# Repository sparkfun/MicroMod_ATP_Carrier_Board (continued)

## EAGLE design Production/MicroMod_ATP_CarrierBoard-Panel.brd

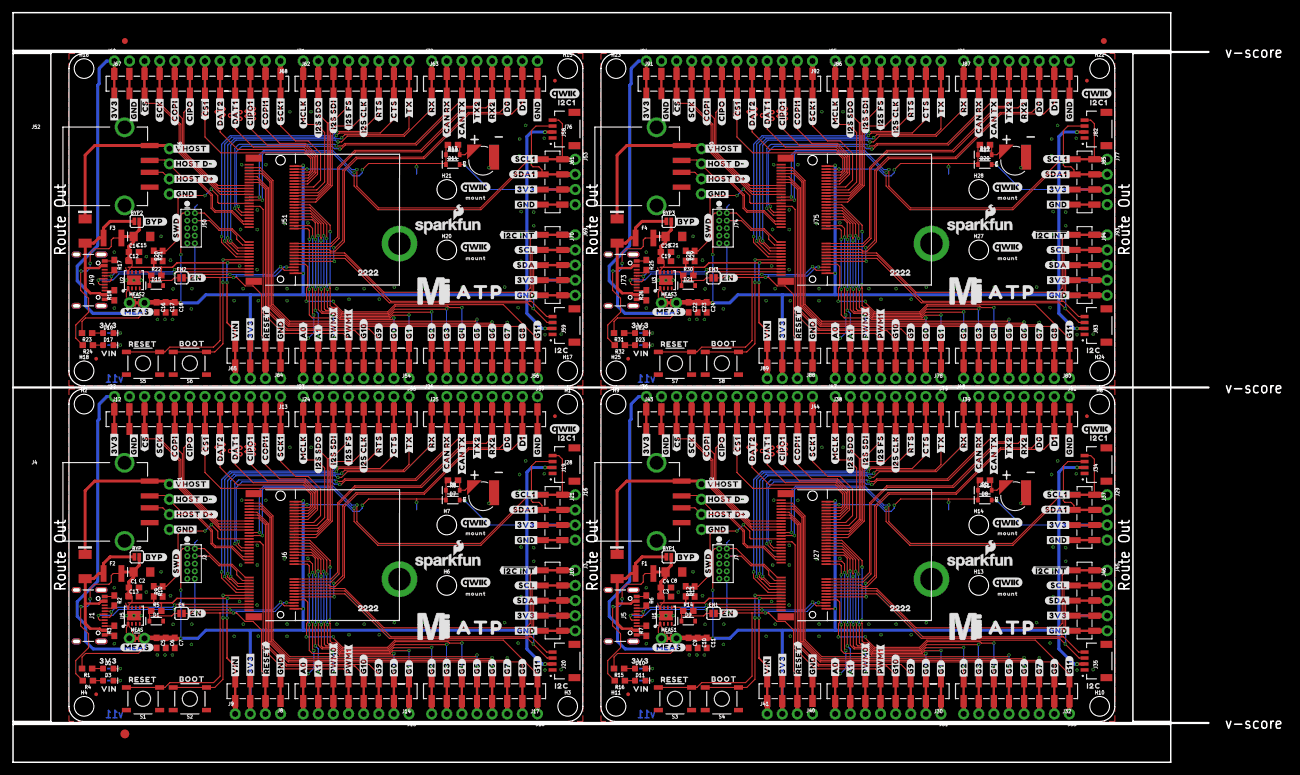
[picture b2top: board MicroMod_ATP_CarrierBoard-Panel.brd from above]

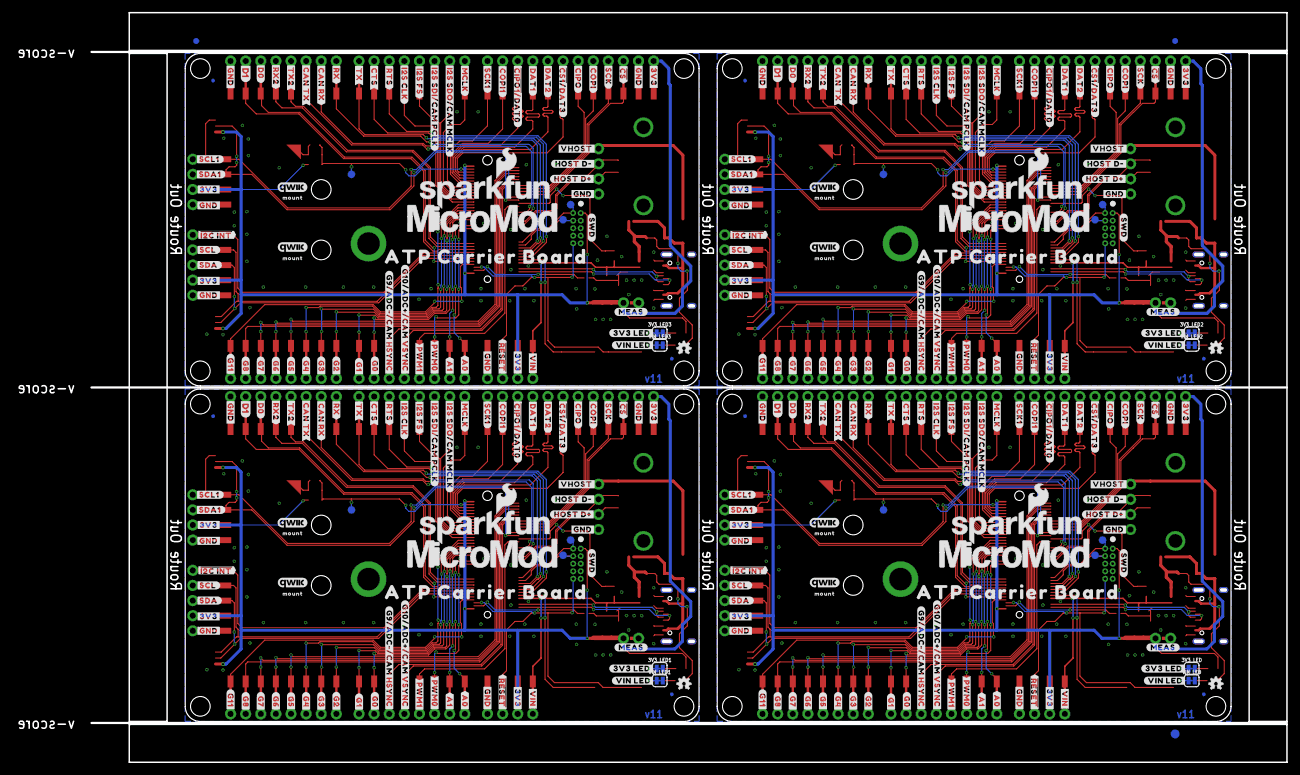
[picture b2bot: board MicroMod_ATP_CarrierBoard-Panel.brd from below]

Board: 2 copper layers, 200.9 x 126.0 mm, 890 parts (323 on the bottom side), 284 nets.

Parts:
3V3_LED, 3V3_LED1, 3V3_LED2, 3V3_LED3: JUMPER-SMT_2_NC_TRACE_SILK; SMT-JUMPER_2_NC_TRACE_SILK
BT1, BT2, BT3, BT4: ML414H; ML414H_IV01E
BYP, BYP1, BYP2, BYP3: JUMPER-SMT_2_NO_SILK; SMT-JUMPER_2_NO_SILK
C1, C4, C6, C10, C14, C17, C20, C23: 0.1uF; 0603
C2, C8, C15, C21: 10uF; EIA3216
C3, C7, C11, C12, C13, C18, C19, C24: 0.22uF; 0603
C5, C9, C16, C22: 1.0uF; 0603
D1, D9, D15, D21: 3.3V; SOD-323
D2, D3, D10, D11, D16, D17, D22, D23: RED; LED-0603
D4, D12, D18, D24: 1A/15V/220mV; DO-214BA
D5, D6, D13, D19: 3A/10V/280mV; SOD-323
D7, D8, D14, D20: 1A/23V/620mV; SOD-323
E$1, E$2, E$3, E$4: FIDUCIAL-1X2
E$5, E$6: FIDUCIAL-1.5X3
EN, EN1, EN2, EN3: JUMPER-SMT_2_NO_SILK; SMT-JUMPER_2_NO_SILK
F1, F2, F3, F4: 6V/2A; 1210
FD1, FD2, FD3, FD4, FD5, FD6, FD7, FD8, FD9, FD10, FD11, FD12, FD13, FD14, FD15, FD16: FIDUCIALUFIDUCIAL; FIDUCIAL-MICRO
H1, H2, H3, H4, H6, H7, H8, H9, H10, H11, H13, H14, H15, H16, H17, H18, H20, H21, H22, H23, H24, H25, H27, H28: STAND-OFF
H5, H12, H19, H26: STAND-OFF-REFLOW2.5MM_TALL; STAND-OFF-REFLOW-M2.5
J1, J5, J49, J73: USB-C-16P-2LAYER-PADS
J2, J7, J50, J74: JTAG; 2X5-PTH-1.27MM
J3, J45, J69, J93: 1X05_NO_SILK
J4, J28, J52, J76: USB_A_SMT_FEMALE; USB-A-S-SILK-FEMALE
J6, J27, J51, J75: MICROMOD-2222-C; M.2-CONNECTOR-E
J8, J21, J37, J40, J61, J64, J85, J88: 1X04_SMD_STRAIGHT_COMBO; 1X04_SMD_VERTICAL_COMBO
J9, J11, J16, J22, J29, J36, J41, J42, J53, J60, J65, J66, J77, J84, J89, J90: 1X04_NO_SILK
J10, J46, J70, J94: 1X05_SMD_VERTICAL_COMBO
J12, J43, J67, J91: 1X12_SMD_COMBINED
J13, J15, J18, J23, J26, J31, J33, J44, J47, J48, J55, J57, J68, J71, J72, J79, J81, J92, J95, J96: 1X08_NO_SILK
J14, J17, J24, J25, J30, J32, J38, J39, J54, J56, J62, J63, J78, J80, J86, J87: 1X08_SMD_COMBINED
J19, J20, J34, J35, J58, J59, J82, J83: QWIIC_RIGHT_ANGLE; JST04_1MM_RA
LOGO1, LOGO11, LOGO19, LOGO27: SFE_LOGO_NAME_FLAME.1_INCH; SFE_LOGO_NAME_FLAME_.1
LOGO2, LOGO15, LOGO23, LOGO31: QWIIC_LOGO_5MM; QWIIC_5MM
LOGO3, LOGO9, LOGO17, LOGO25: OSHW-LOGOMINI; OSHW-LOGO-MINI
LOGO4, LOGO10, LOGO18, LOGO26: SFE_LOGO_NAME_FLAME.2_INCH; SFE_LOGO_NAME_FLAME_.2
LOGO5, LOGO6, LOGO7, LOGO8, LOGO12, LOGO13, LOGO14, LOGO16, LOGO20, LOGO21, LOGO22, LOGO24, LOGO28, LOGO29, LOGO30, LOGO32: QWIIC_LOGO_3MM; QWIIC_5MM
MEAS, MEAS1, MEAS2, MEAS3: COMBO-JUMPER_2_NC_TRACE
R1, R4, R8, R11, R15, R16, R19, R23, R24, R27, R31, R32: 1k; 0603
R2, R3, R6, R7, R17, R18, R25, R26: 5.1k; 0603
R5, R14, R22, R30: 100k; 0603
R9, R12, R20, R28: 10k; 0603
R10, R13, R21, R29: 20k; 0603
S1, S3, S5, S7: Reset; TACTILE_SWITCH_SMD_5.2MM
S2, S4, S6, S8: BOOT; TACTILE_SWITCH_SMD_5.2MM
TP1, TP2, TP3, TP4, TP5, TP6, TP7, TP8, TP9, TP10, TP11, TP12: TEST-POINT3X5; PAD.03X.05
U1, U2, U3, U5: AP7361C-33; UDFN-8
U$1, U$123, U$169, U$251, U$314, U$396, U$459, U$541: #A0#10
U$2, U$124, U$170, U$252, U$315, U$397, U$460, U$542: #A1#10
U$3, U$27, U$46, U$47, U$58, U$89, U$100, U$101, U$102, U$103, U$104, U$105, U$160, U$166, U$167, U$228, U$229, U$230, U$231, U$232, U$233, U$268, U$269, U$270, U$305, U$311, U$312, U$373, U$374, U$375, U$376, U$377, U$378, U$413, U$414, U$415, U$450, U$456, U$457, U$518, U$519, U$520, U$521, U$522, U$523, U$558, U$559, U$560: #GND#0
U$4, U$120, U$172, U$248, U$317, U$393, U$462, U$538: #G0#2
U$5, U$163, U$308, U$453: #RESET10
U$6, U$98, U$171, U$227, U$316, U$372, U$461, U$517: #D0#0
U$7, U$119, U$173, U$247, U$318, U$392, U$463, U$537: #G1#2
U$8, U$118, U$174, U$246, U$319, U$391, U$464, U$536: #G2#2
U$9, U$117, U$175, U$245, U$320, U$390, U$465, U$535: #G3#3
U$10, U$116, U$176, U$244, U$321, U$389, U$466, U$534: #G4#4
U$11, U$115, U$177, U$243, U$322, U$388, U$467, U$533: #G5#5
U$12, U$114, U$178, U$242, U$323, U$387, U$468, U$532: #G6#6
U$13, U$113, U$179, U$241, U$324, U$386, U$469, U$531: #G7#7
U$14, U$112, U$180, U$240, U$325, U$385, U$470, U$530: #G8#8
U$15, U$181, U$326, U$471: #G9#9
U$16, U$182, U$327, U$472: #G10#10
U$17, U$111, U$183, U$239, U$328, U$384, U$473, U$529: #G11#10
U$18, U$121, U$184, U$249, U$329, U$394, U$474, U$539: #PWM0#10
U$19, U$122, U$185, U$250, U$330, U$395, U$475, U$540: #PWM1#10
U$20, U$286, U$431, U$576: ##CS1##5178039
U$21, U$110, U$238, U$271, U$383, U$416, U$528, U$561: ##I2C_INT##10
U$22, U$130, U$292, U$437: #CAN_RX#9
U$23, U$97, U$148, U$226, U$293, U$371, U$438, U$516: #CAN_TX#10
U$24, U$149, U$294, U$439: #CIPO#3
U$25, U$150, U$295, U$440: #COPI#2
U$26, U$151, U$296, U$441: #CTS#6
U$28, U$267, U$412, U$557: #SCK#2
U$29, U$152, U$297, U$442: #I2S_FS#5
U$30, U$153, U$298, U$443: #I2S_SDI#5
U$31, U$154, U$299, U$444: #I2S_SDO#5
U$32, U$155, U$300, U$445: #MCLK#4
U$33, U$156, U$301, U$446: #RTS#5
U$34, U$157, U$302, U$447: #RX#8
U$35, U$158, U$303, U$448: #TX#7
U$36, U$287, U$432, U$577: #DAT1#5178039
U$37, U$125, U$206, U$253, U$351, U$398, U$496, U$543: ##RESET##7
U$38, U$60, U$61, U$70, U$88, U$106, U$107, U$126, U$197, U$198, U$199, U$200, U$234, U$235, U$254, U$266, U$342, U$343, U$344, U$345, U$379, U$380, U$399, U$411, U$487, U$488, U$489, U$490, U$524, U$525, U$544, U$556: #3V3#1
U$39, U$159, U$304, U$449: #BYP#8
U$40, U$128, U$161, U$256, U$306, U$401, U$451, U$546: #HOST_D##9
U$41, U$129, U$162, U$257, U$307, U$402, U$452, U$547: #HOST_D##10
U$42, U$132, U$186, U$259, U$331, U$404, U$476, U$549: #MEAS#10
U$43, U$164, U$309, U$454: BOOT10
U$44, U$108, U$187, U$236, U$332, U$381, U$477, U$526: #SDA#4
U$45, U$127, U$165, U$255, U$310, U$400, U$455, U$545: #VIN#6
U$48, U$280, U$425, U$570: #EN#0
U$49, U$109, U$168, U$237, U$313, U$382, U$458, U$527: #SCL#5
U$50, U$146, U$281, U$282, U$426, U$427, U$571, U$572: #VHOST#0
U$51, U$131, U$188, U$258, U$333, U$403, U$478, U$548: #SWD#10
U$52, U$189, U$334, U$479: #I2S_CLK#5
U$53, U$288, U$433, U$578: #DAT2#5178039
U$54, U$289, U$434, U$579: #CIPO1#5178039
U$55, U$74, U$291, U$436: 22229
U$56, U$290, U$435, U$580: ##CIPO1##DAT0#5178038
U$57, U$75, U$205, U$208, U$350, U$353, U$495, U$498: #COPI1#2
U$59, U$207, U$352, U$497: ##CS##0
U$62, U$201, U$346, U$491: ATP0
U$63, U$76, U$190, U$209, U$335, U$354, U$480, U$499: #RX2#3
U$64, U$80, U$191, U$213, U$336, U$358, U$481, U$503: #TX2#2
U$65, U$78, U$192, U$211, U$337, U$356, U$482, U$501: #SCL1#3
U$66, U$79, U$193, U$212, U$338, U$357, U$483, U$502: #SDA1#3
U$67, U$77, U$194, U$210, U$339, U$355, U$484, U$500: #SCK1#2
U$68, U$195, U$340, U$485: VIN3
U$69, U$196, U$341, U$486: 3V34
U$71, U$202, U$347, U$492: I2C4
U$72, U$203, U$348, U$493: I2C14
U$73, U$204, U$349, U$494: ATP_CARRIER_BOARD1
U$81, U$283, U$428, U$573: ##CS##5178037
U$82, U$214, U$359, U$504: #DAT2#5
U$83, U$215, U$360, U$505: #DAT1#5
U$84, U$284, U$429, U$574: ##CS1##DAT3#5178037
U$85, U$216, U$361, U$506: #COPI#4
U$86, U$217, U$362, U$507: #SCK#4
U$87, U$218, U$363, U$508: #MCLK#6
U$90, U$219, U$364, U$509: #I2S_FS#7
U$91, U$220, U$365, U$510: #I2S_CLK#7
U$92, U$221, U$366, U$511: #RTS#7
U$93, U$222, U$367, U$512: #CTS#8
U$94, U$223, U$368, U$513: #TX#9
U$95, U$224, U$369, U$514: #RX#10
U$96, U$225, U$370, U$515: #CAN_RX#10
U$99, U$145, U$272, U$279, U$417, U$424, U$562, U$569: D10
U$133, U$260, U$405, U$550: #VIN_LED#10
U$134, U$261, U$406, U$551: #3V3_LED#10
U$135, U$262, U$407, U$552: #G9#ADC##CAM_HSYNC#9
U$136, U$263, U$408, U$553: #G10#ADC##CAM_VSYNC#10
U$137, U$264, U$409, U$554: #I2S_SDI#CAM_PCLK#7
U$138, U$265, U$410, U$555: #I2S_SDO#CAM_MCLK#7
U$139, U$141, U$142, U$143, U$274, U$275, U$276, U$277, U$419, U$420, U$421, U$422, U$564, U$565, U$566, U$567: MOUNT10
U$140, U$273, U$418, U$563: MICROMOD_MI_LOGO_1
U$144, U$278, U$423, U$568: MICROMOD_LOGO_1
U$147, U$285, U$430, U$575: #CIPO#5178038
VIN_LED, VIN_LED1, VIN_LED2, VIN_LED3: JUMPER-SMT_2_NC_TRACE_SILK; SMT-JUMPER_2_NC_TRACE_SILK

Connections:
3.3V: C5.1, C6.1, C7.1, D7.A, J2.1, J3.4, J6.2, J6.74, J8.3, J9.2, J10.4, J12.1, J16.3, J19.2, J20.2, J21.3, J22.1, MEAS.2, MEAS.4, R1.2
3.3V1: C9.1, C10.1, C11.1, D8.A, J7.1, J27.2, J27.74, J29.3, J34.2, J35.2, J36.1, J37.3, J40.3, J41.2, J43.1, J45.4, J46.4, MEAS1.2, MEAS1.4, R15.2
3.3V2: C16.1, C17.1, C18.1, D14.A, J50.1, J51.2, J51.74, J53.3, J58.2, J59.2, J60.1, J61.3, J64.3, J65.2, J67.1, J69.4, J70.4, MEAS2.2, MEAS2.4, R23.2
3.3V3: C22.1, C23.1, C24.1, D20.A, J74.1, J75.2, J75.74, J77.3, J82.2, J83.2, J84.1, J85.3, J88.3, J89.2, J91.1, J93.4, J94.4, MEAS3.2, MEAS3.4, R31.2
3.3V_EN: D1.C, EN.1, R5.1, U5.5
3.3V_EN1: D9.C, EN1.1, R14.1, U1.5
3.3V_EN2: D15.C, EN2.1, R22.1, U2.5
3.3V_EN3: D21.C, EN3.1, R30.1, U3.5
!BOOT!: J6.11, S2.3, S2.4
!BOOT!1: J27.11, S4.3, S4.4
!BOOT!2: J51.11, S6.3, S6.4
!BOOT!3: J75.11, S8.3, S8.4
!CS1!/DAT1: J27.70, J43.7, J44.6
!CS1!/DAT2: J51.70, J67.7, J68.6
!CS1!/DAT3: J6.70, J12.7, J13.6
!CS1!/DAT4: J75.70, J91.7, J92.6
!CS!: J6.55, J12.3, J22.3
!CS!1: J27.55, J36.3, J43.3
!CS!2: J51.55, J60.3, J67.3
!CS!3: J75.55, J84.3, J91.3
!RESET: J2.10, J6.6, J8.2, J9.3, S1.3, S1.4
!RESET1: J7.10, J27.6, J40.2, J41.3, S3.3, S3.4
!RESET2: J50.10, J51.6, J64.2, J65.3, S5.3, S5.4
!RESET3: J74.10, J75.6, J88.2, J89.3, S7.3, S7.4
A0: J6.34, J14.8, J15.8
A1: J6.38, J14.7, J15.7
A2: J27.34, J30.8, J31.8
A3: J27.38, J30.7, J31.7
A4: J51.34, J54.8, J55.8
A5: J51.38, J54.7, J55.7
A6: J75.34, J78.8, J79.8
A7: J75.38, J78.7, J79.7
CAN_RXI: J6.41, J25.2, J26.2
CAN_RXI1: J27.41, J39.2, J48.2
CAN_RXI2: J51.41, J63.2, J72.2
CAN_RXI3: J75.41, J87.2, J96.2
CAN_TXO: J6.43, J25.3, J26.3
CAN_TXO1: J27.43, J39.3, J48.3
CAN_TXO2: J51.43, J63.3, J72.3
CAN_TXO3: J75.43, J87.3, J96.3
CIPO: J6.61, J12.6, J13.7
CIPO1: J27.61, J43.6, J44.7
CIPO1/DAT0: J6.64, J12.10, J13.3
CIPO1/DAT1: J27.64, J43.10, J44.3
CIPO1/DAT2: J51.64, J67.10, J68.3
CIPO1/DAT3: J75.64, J91.10, J92.3
CIPO2: J51.61, J67.6, J68.7
CIPO3: J75.61, J91.6, J92.7
COPI: J6.59, J12.5, J13.8
COPI1: J6.62, J12.11, J13.2
COPI2: J27.59, J43.5, J44.8
COPI3: J27.62, J43.11, J44.2
COPI4: J51.59, J67.5, J68.8
COPI5: J51.62, J67.11, J68.2
COPI6: J75.59, J91.5, J92.8
COPI7: J75.62, J91.11, J92.2
CTS1: J6.15, J23.7, J24.7
CTS2: J27.15, J38.7, J47.7
CTS3: J51.15, J62.7, J71.7
CTS4: J75.15, J86.7, J95.7
D0: J6.10, J25.6, J26.6
D1: J6.18, J25.7, J26.7
D2: J27.10, J39.6, J48.6
D3: J27.18, J39.7, J48.7
D4: J51.10, J63.6, J72.6
D5: J51.18, J63.7, J72.7
D6: J75.10, J87.6, J96.6
D7: J75.18, J87.7, J96.7
DAT1: J6.66, J12.9, J13.4
DAT2: J6.68, J12.8, J13.5
DAT3: J27.66, J43.9, J44.4
DAT4: J27.68, J43.8, J44.5
DAT5: J51.66, J67.9, J68.4
DAT6: J51.68, J67.8, J68.5
DAT7: J75.66, J91.9, J92.4
DAT8: J75.68, J91.8, J92.5
G0: J6.40, J14.2, J15.2
G1: J6.42, J14.1, J15.1
G2: J6.44, J17.8, J18.8
G3: J6.46, J17.7, J18.7
G4: J6.48, J17.6, J18.6
G5: J6.73, J17.5, J18.5
G6: J6.71, J17.4, J18.4
G7: J6.69, J17.3, J18.3
G8: J6.67, J17.2, J18.2
G9: J27.40, J30.2, J31.2
G9/ADC_N: J6.65, J14.3, J15.3
G9/ADC_N1: J27.65, J30.3, J31.3
G9/ADC_N2: J51.65, J54.3, J55.3
G9/ADC_N3: J75.65, J78.3, J79.3
G10: J27.42, J30.1, J31.1
G10/ADC_P: J6.63, J14.4, J15.4
G10/ADC_P1: J27.63, J30.4, J31.4
G10/ADC_P2: J51.63, J54.4, J55.4
G10/ADC_P3: J75.63, J78.4, J79.4
G11: J6.8, J17.1, J18.1
G12: J27.73, J32.5, J33.5
G13: J27.48, J32.6, J33.6
G14: J27.44, J32.8, J33.8
G15: J27.69, J32.3, J33.3
G16: J27.46, J32.7, J33.7
G17: J27.71, J32.4, J33.4
G18: J27.67, J32.2, J33.2
G19: J27.8, J32.1, J33.1
G20: J51.40, J54.2, J55.2
G21: J51.42, J54.1, J55.1
G22: J51.73, J56.5, J57.5
G23: J51.48, J56.6, J57.6
G24: J51.44, J56.8, J57.8
G25: J51.69, J56.3, J57.3
G26: J51.46, J56.7, J57.7
G27: J51.71, J56.4, J57.4
G28: J51.67, J56.2, J57.2
G29: J51.8, J56.1, J57.1
G30: J75.40, J78.2, J79.2
G31: J75.42, J78.1, J79.1
G32: J75.73, J80.5, J81.5
G33: J75.48, J80.6, J81.6
G34: J75.44, J80.8, J81.8
G35: J75.69, J80.3, J81.3
G36: J75.46, J80.7, J81.7
G37: J75.71, J80.4, J81.4
G38: J75.67, J80.2, J81.2
G39: J75.8, J80.1, J81.1
GND: 3V3_LED.2, BT1.-, C1.2, C2.-, C5.2, C6.2, C7.2, C13.2, D1.A, H5.1, J1.GND, J1.GND2, J2.3, J2.5, J2.9, J3.5, J4.GND, J4.SHLD1, J4.SHLD2, J6.1, J6.7, J6.33, J6.36, J6.39, J6.45, J6.75, J8.1, J9.4, J10.5, J11.4, J12.2, J16.4, J19.1, J20.1, J21.4, J22.2, J25.8, J26.8, R2.1, R3.1, R9.1, S1.1, S1.2, S2.1, S2.2, U5.4, U5.EP, VIN_LED.2
GND1: 3V3_LED1.2, BT2.-, C3.2, C4.2, C8.-, C9.2, C10.2, C11.2, D9.A, H12.1, J5.GND, J5.GND2, J7.3, J7.5, J7.9, J27.1, J27.7, J27.33, J27.36, J27.39, J27.45, J27.75, J28.GND, J28.SHLD1, J28.SHLD2, J29.4, J34.1, J35.1, J36.2, J37.4, J39.8, J40.1, J41.4, J42.4, J43.2, J45.5, J46.5, J48.8, R6.1, R7.1, R12.1, S3.1, S3.2, S4.1, S4.2, U1.4, U1.EP, VIN_LED1.2
GND2: 3V3_LED2.2, BT3.-, C12.2, C14.2, C15.-, C16.2, C17.2, C18.2, D15.A, H19.1, J49.GND, J49.GND2, J50.3, J50.5, J50.9, J51.1, J51.7, J51.33, J51.36, J51.39, J51.45, J51.75, J52.GND, J52.SHLD1, J52.SHLD2, J53.4, J58.1, J59.1, J60.2, J61.4, J63.8, J64.1, J65.4, J66.4, J67.2, J69.5, J70.5, J72.8, R17.1, R18.1, R20.1, S5.1, S5.2, S6.1, S6.2, U2.4, U2.EP, VIN_LED2.2
GND3: 3V3_LED3.2, BT4.-, C19.2, C20.2, C21.-, C22.2, C23.2, C24.2, D21.A, H26.1, J73.GND, J73.GND2, J74.3, J74.5, J74.9, J75.1, J75.7, J75.33, J75.36, J75.39, J75.45, J75.75, J76.GND, J76.SHLD1, J76.SHLD2, J77.4, J82.1, J83.1, J84.2, J85.4, J87.8, J88.1, J89.4, J90.4, J91.2, J93.5, J94.5, J96.8, R25.1, R26.1, R28.1, S7.1, S7.2, S8.1, S8.2, U3.4, U3.EP, VIN_LED3.2
I2C_!INT: J3.1, J6.16, J10.1
I2C_!INT1: J27.16, J45.1, J46.1
I2C_!INT2: J51.16, J69.1, J70.1
I2C_!INT3: J75.16, J93.1, J94.1
I2S_CLK: J6.50, J23.5, J24.5
I2S_CLK1: J27.50, J38.5, J47.5
I2S_CLK2: J51.50, J62.5, J71.5
I2S_CLK3: J75.50, J86.5, J95.5
I2S_SDI: J6.54, J23.3, J24.3
I2S_SDI1: J27.54, J38.3, J47.3
I2S_SDI2: J51.54, J62.3, J71.3
I2S_SDI3: J75.54, J86.3, J95.3
I2S_SDO: J6.56, J23.2, J24.2
I2S_SDO1: J27.56, J38.2, J47.2
I2S_SDO2: J51.56, J62.2, J71.2
I2S_SDO3: J75.56, J86.2, J95.2
I2S_WS: J6.52, J23.4, J24.4
I2S_WS1: J27.52, J38.4, J47.4
I2S_WS2: J51.52, J62.4, J71.4
I2S_WS3: J75.52, J86.4, J95.4
MCLK: J6.58, J23.1, J24.1
MCLK1: J27.58, J38.1, J47.1
MCLK2: J51.58, J62.1, J71.1
MCLK3: J75.58, J86.1, J95.1
unnamed: D2.A, R1.1
unnamed: D3.A, R4.1
unnamed: 3V3_LED.1, D2.C
unnamed: D3.C, VIN_LED.1
unnamed: EN.2, J6.4
unnamed: J5.A5, R6.2
unnamed: D4.C, J4.VBUS, J11.1
unnamed: J5.B5, R7.2
unnamed: BT2.+, D5.A, R11.1
unnamed: J1.A5, R2.2
unnamed: J1.B5, R3.2
unnamed: D10.A, R15.1
unnamed: D11.A, R16.1
unnamed: BT1.+, D6.A, R8.1
unnamed: 3V3_LED1.1, D10.C
unnamed: D11.C, VIN_LED1.1
unnamed: EN1.2, J27.4
unnamed: D12.C, J28.VBUS, J42.1
unnamed: J49.A5, R17.2
unnamed: J49.B5, R18.2
unnamed: BT3.+, D13.A, R19.1
unnamed: D16.A, R23.1
unnamed: D17.A, R24.1
unnamed: 3V3_LED2.1, D16.C
unnamed: D17.C, VIN_LED2.1
unnamed: EN2.2, J51.4
unnamed: D18.C, J52.VBUS, J66.1
unnamed: J73.A5, R25.2
unnamed: J73.B5, R26.2
unnamed: BT4.+, D19.A, R27.1
unnamed: D22.A, R31.1
unnamed: D23.A, R32.1
unnamed: 3V3_LED3.1, D22.C
unnamed: D23.C, VIN_LED3.1
unnamed: EN3.2, J75.4
unnamed: D24.C, J76.VBUS, J90.1
OUT_MEAS: MEAS.1, MEAS.3, U5.1
OUT_MEAS1: MEAS1.1, MEAS1.3, U1.1
OUT_MEAS2: MEAS2.1, MEAS2.3, U2.1
OUT_MEAS3: MEAS3.1, MEAS3.3, U3.1
PWM0: J6.32, J14.6, J15.6
PWM1: J6.47, J14.5, J15.5
PWM2: J27.32, J30.6, J31.6
PWM3: J27.47, J30.5, J31.5
PWM4: J51.32, J54.6, J55.6
PWM5: J51.47, J54.5, J55.5
PWM6: J75.32, J78.6, J79.6
PWM7: J75.47, J78.5, J79.5
RTC_3V: D6.C, D7.C, J6.72, R8.2, TP1.P$1
RTC_3V1: D5.C, D8.C, J27.72, R11.2, TP4.P$1
RTC_3V2: D13.C, D14.C, J51.72, R19.2, TP7.P$1
RTC_3V3: D19.C, D20.C, J75.72, R27.2, TP10.P$1
RTS1: J6.13, J23.6, J24.6
RTS2: J27.13, J38.6, J47.6
RTS3: J51.13, J62.6, J71.6
RTS4: J75.13, J86.6, J95.6
RX1: J6.19, J25.1, J26.1
RX2: J6.20, J25.5, J26.5
RX3: J27.19, J39.1, J48.1
RX4: J27.20, J39.5, J48.5
RX5: J51.19, J63.1, J72.1
RX6: J51.20, J63.5, J72.5
RX7: J75.19, J87.1, J96.1
RX8: J75.20, J87.5, J96.5
SCK: J6.57, J12.4, J22.4
SCK1: J6.60, J12.12, J13.1
SCK2: J27.57, J36.4, J43.4
SCK3: J27.60, J43.12, J44.1
SCK4: J51.57, J60.4, J67.4
SCK5: J51.60, J67.12, J68.1
SCK6: J75.57, J84.4, J91.4
SCK7: J75.60, J91.12, J92.1
SCL: J3.2, J6.14, J10.2, J20.4
SCL1: J6.53, J16.1, J19.4, J21.1
SCL2: J27.14, J35.4, J45.2, J46.2
SCL3: J27.53, J29.1, J34.4, J37.1
SCL4: J51.14, J59.4, J69.2, J70.2
SCL5: J51.53, J53.1, J58.4, J61.1
SCL6: J75.14, J83.4, J93.2, J94.2
SCL7: J75.53, J77.1, J82.4, J85.1
SDA: J3.3, J6.12, J10.3, J20.3
SDA1: J6.51, J16.2, J19.3, J21.2
SDA2: J27.12, J35.3, J45.3, J46.3
SDA3: J27.51, J29.2, J34.3, J37.2
SDA4: J51.12, J59.3, J69.3, J70.3
SDA5: J51.51, J53.2, J58.3, J61.2
SDA6: J75.12, J83.3, J93.3, J94.3
SDA7: J75.51, J77.2, J82.3, J85.2
SWDCK: J2.4, J6.21, TP3.P$1
SWDCK1: J7.4, J27.21, TP6.P$1
SWDCK2: J50.4, J51.21, TP9.P$1
SWDCK3: J74.4, J75.21, TP12.P$1
SWDIO: J2.2, J6.23, TP2.P$1
SWDIO1: J7.2, J27.23, TP5.P$1
SWDIO2: J50.2, J51.23, TP8.P$1
SWDIO3: J74.2, J75.23, TP11.P$1
TX1: J6.17, J23.8, J24.8
TX2: J6.22, J25.4, J26.4
TX3: J27.17, J38.8, J47.8
TX4: J27.22, J39.4, J48.4
TX5: J51.17, J62.8, J71.8
TX6: J51.22, J63.4, J72.4
TX7: J75.17, J86.8, J95.8
TX8: J75.22, J87.4, J96.4
USBHOST_N: J4.D-, J6.37, J11.2
USBHOST_N1: J27.37, J28.D-, J42.2
USBHOST_N2: J51.37, J52.D-, J66.2
USBHOST_N3: J75.37, J76.D-, J90.2
USBHOST_P: J4.D+, J6.35, J11.3
USBHOST_P1: J27.35, J28.D+, J42.3
USBHOST_P2: J51.35, J52.D+, J66.3
USBHOST_P3: J75.35, J76.D+, J90.3
USB_N: J1.A7, J1.B7, J6.5
USB_N1: J5.A7, J5.B7, J27.5
USB_N2: J49.A7, J49.B7, J51.5
USB_N3: J73.A7, J73.B7, J75.5
USB_P: J1.A6, J1.B6, J6.3
USB_P1: J5.A6, J5.B6, J27.3
USB_P2: J49.A6, J49.B6, J51.3
USB_P3: J73.A6, J73.B6, J75.3
VIN: BYP.2, C1.1, C2.+, C13.1, F2.2, J6.9, J8.4, J9.1, R4.2, R5.2, R10.2, U5.8
VIN1: BYP1.2, C3.1, C4.1, C8.+, F1.2, J27.9, J40.4, J41.1, R13.2, R14.2, R16.2, U1.8
VIN2: BYP2.2, C12.1, C14.1, C15.+, F3.2, J51.9, J64.4, J65.1, R21.2, R22.2, R24.2, U2.8
VIN3: BYP3.2, C19.1, C20.1, C21.+, F4.2, J75.9, J88.4, J89.1, R29.2, R30.2, R32.2, U3.8
VIN/1: J27.49, R12.2, R13.1
VIN/2: J51.49, R20.2, R21.1
VIN/3: J6.49, R9.2, R10.1
VIN/4: J75.49, R28.2, R29.1
V_USB: BYP.1, D4.A, F2.1, J1.VBUS1, J1.VBUS2
V_USB1: BYP1.1, D12.A, F1.1, J5.VBUS1, J5.VBUS2
V_USB2: BYP2.1, D18.A, F3.1, J49.VBUS1, J49.VBUS2
V_USB3: BYP3.1, D24.A, F4.1, J73.VBUS1, J73.VBUS2

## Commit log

2020-06-01 Many headers added, netted, and placed into form factor
2020-06-02 Trace work for ATP board
2020-06-03 Adds barrel jack for power
2020-07-22 "Reverts" back to a time when barrel jack did not exist
2020-07-22 Shrinks board, adds routing
    * board is now 2 x 3 roughly
    * Added a longer header for MCLK and GND -> went from 10-12 pin
    * Routed SPI, QSPI, and I2S
2020-07-23 Routes the Analog and RX2 traces
2020-07-23 Routes Serial, I2C, and CAN lines
2020-07-23 Reorders the "G#" lines and moves traces so that they hit at 90 degrees
2020-07-23 Moves a few traces - again for 90 degree intersections
2020-07-23 Shifts top header assignements to the left to make space for 3v3 and GND pins
    * Adds top silk to almost all pins
2020-07-24 Adds the rest of the header labels, fixes or approves DRC errors
    * adds Qwiic Mount screw holes
2020-07-24 Renames LED jumpers to their function
2020-07-24 Miters the corners of the board
2020-07-25 Swaps qwiic connectors and their respective headers
    * Moves headers on teh top and bottom so that they can be placed properly
    * Moves the USB host and USB-C connector down so that labels on teh top can fit
    * adjusts the traces accordingly to the part movement
2020-07-25 Moves GND and 3V3 label on top of board along topside of PCB
2020-07-27 Changes silk labels to bi-directional on G# lines, fixes INPUT/OUTPUT labels on
    RTS, CTS, A#, and PWM lines
2020-07-27 Replaces all connectors with their updated version
2020-07-27 Matches length on the QSPI lines
2020-07-27 Swaps one 8 pin header in the test lib to on from the main Sparkfun lib
2020-07-28 Swaps out smaller qwiic labels for larger ones
2020-07-28 Adds testpoint for the RTC lines, adds text for VIN range and warning about using USB host and USB-C at the same time
2020-07-28 Adds a normally open enable jumper to 3.3V EN
2020-07-29 Adds gerber production files.
2020-07-29 Gives some space in between data lines
2020-07-29 Adds a diode with 220mV Vf to protect back voltage from USB-Host (just in case)
2020-07-29 Changes silk "VUSB" to "VHOST" moves some traces around USB-C to make some space
2020-07-30 Adds a few vias
2020-07-30 Update panel
2020-07-30 Changes production board size to 2x2 instead of 1x4
2020-08-21 Updates SKU on 1x5 connector
2020-08-25 Update M.2 Connector and repanelizes for production
2020-09-10 Updates micromod female connector and renames nets
2020-09-10 Updates silk, fixes Qwiic connector wiring
2020-09-10 Updates production files
2020-09-11 Revert "Updates production files"
    This reverts commit 213e6b1cbeb41024665e9e154624d95cc9d0b3ef.
2020-09-15 Fixes some proportional font, swaps SDA and SCL on I2C qwiic connector, adds additional qwiic logo
2020-09-16 Updates production files with new silk and qwiic connector fixes
